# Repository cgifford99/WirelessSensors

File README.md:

# WirelessSensors
Wireless Sensors Flex Friday project repo

Here's a link to our Waffle.io management board: https://waffle.io/cgifford99/WirelessSensors/join

## Current Schedule
- [x] Project Proposal  | September 11th-September 30th
- [x] Research          | September 30th-October 7th
- [ ] Data pro design   | October 7th- December 23rd
- [ ] Testing/Debugging | December 23rd-April 7th 2017
- [ ] Finalize product  | March 3rd 2017-May 19th 2017
- [ ] Presentation      | May 19th 2017-June 9th 2017

# Wireless Sensors Proposal
## Abstract
The Wireless Sensor group’s overall goal is to create an easier and more cost-effective way to wirelessly transmit data from classroom   experiments from sensors through a communication chip to internet-enabled devices such as computers, laptops, tablets and smartphones. This system will allow students to easily customize how data is collected and manipulate data to fit their needs. It also allows teachers to view   the student’s data. Although this system will be useful in many fields, the project is going to initially focus on the educational market. This technology currently exists from other corporations, but it’s slow, expensive, complicated and unreliable. The team’s alternative will be faster, less expensive, user friendly and will deliver consistent results again and again. Furthermore, the current systems use wires, that get tangled and get lost. All of these wires can be eliminated with the use of radio communication and this is what the Wireless Sensor Team plans to do.

## Problem Statement
Currently there is no easy way to collect, store and share data from classroom science experiments simply by running the experiment and having data automatically appear on a shared website using low-cost components and inexpensive, yet effective software. Vernier is a company that produces a product along the lines of what we are creating, but it’s expensive, slow, and hard to access data. Products produced by Vernier, such as LabQuest, cost over $300 and need the use of another source, such as a PC, to process the collected data.

## Goals and Objectives
* Goal 1: Create a working prototype that sends information from a Raspberry Pi Zero/Arduino Micro to a Raspberry Pi 3.

  * Objective A: Discuss what teams are necessary, what project managing software to use, whether to use a Raspberry Pi Zero or an Arduino Micro to control the sensors and whether to make another prototype for the Rpi Zero or not.
  * Objective B: If the Rpi Zero is going to be used, code will need to be converted from the Arduino C++ language to C++ on the Rpi Zero.
  * Objective C: Create a prototype that includes the necessary components to interact with the Rpi 3 (the Hub).
  * Objective D: Debug data collection process and code (if necessary).

* Goal 2: Develop a cloud-based software for data storage and data transfer.

  * Objective A: Study Flask-SQLAlchemy (a framework to connect to a SQL database on the Rpi 3 and a browser on another device)
  * Objective B: Create and test a connection between the Rpi 3 SQL database and Flask-SQLAlchemy

* Goal 3: Finalize the product so that it both looks and works well for users.

  * Objective A: Design, order and solder a PCB (printed circuit board) that integrates with the Rpi Zero as well as the Rpi 3 in a more compact and visually attractive method.
  * Objective B: Use solidworks or another 3D design software to design an enclosure for the Rpi 3 and the Rpi Zero/Arduino Micro.
  * Objective C: Complete, debug and finish the product.
  
## Our Team
**Christopher Gifford**: Christopher is a Junior and project manager of the Wireless Sensors group. Last year he managed the sensors portion of the wireless group and learned a variety of other skills like 3D design, PCB design, and more C++ programming since then. 

**Lewis Woodard**: Lewis is a Sophomore at Baxter Academy for Technology and Science who is a part of the Wireless Sensors project for the second year. He hopes to focus his efforts in the project towards hardware and enclosures, which will include PCB design and using SolidWorks to design enclosures, cases, and other devices to contain sensors. Last year Lewis joined after completing the Pentathlon and worked on a combination of hardware, enclosures and software. Since last year, Lewis has gained more experience in C++ programming, CAD and more. Lewis plans to use this knowledge to focus mainly on hardware, pcb and 3D design, assisting on programming and software when he is needed.

**Connor Bell**: (NOTE: Connor is no longer involved with the project) Connor is a Junior at Baxter Academy for Technology and Science. He is a new addition to the Wireless Sensors project. He has taken multiple classes based around electronics and computer programming, and is currently learning as much as he can to have enough knowledge to be successful on this projects. Connor has programmed multiple web-based and non-web based programs in various languages such as Python and Javascript, both of which are relevant to the progress of this project.

**Curtis**: 
Curtis is a Sophomore at Baxter Academy for Technology and Science. He is also a new addition to the Wireless Sensors project. He has taken multiple classes based around electronics and computer programming. Curtis plans to concentrate on programming so that he be a productive member of the group.

**Ryan Cunningham**: Ryan is a freshman a Baxter. He is also a new addition to the Wireless Sensors project. He has lots of experience in HTML and CSS, he also is skilled in GUI design and graphics works. 

## Timeline
Currently unavailable

## Resources
* The school has tools like 3d printing software and equipment, soldering irons and other useful PCB design tools.
* Alan Lukas, Hal, Wells and Amory have backgrounds in programming, 3D design and PCB design and their knowledge will be very useful in the project.
* Currently an arduino prototype (Sensor prototype) and a Raspberry Pi 3 prototype (Hub prototype), are functioning from last year.    However, the Arduino did not have sufficient memory to hold a large number of different data acquisition formats.    The current plan is to use a RPi Zero instead for the Arduino for the sensor prototype.
* Purchase a  variety of Vernier sensors or borrow them as required from Baxter’s inventory.

## Constraints
* The team’s experience in PCB design, C++ programming, 3D design and other skill sets will influence how smoothly the project goes.
* There is not enough time this year to set-up a business and market the product to schools and other educational services.
* Accidents like damaging the circuits or short-circuiting them has been a problem in the past.
* There will be plenty of distractions and time constraints, but the team will use detailed schedules (Kanban and Gantter) to stay on track.

## Budget
Currently unavailable

## Deliverables
The final product will be a marketable platform to use in a classroom environment for experiments and laboratory tests in different subjects including physics, chemistry, and others. It will be made up of a Raspberry Pi Zeros (sensors) and a larger Raspberry Pi (hub). The hub will store and organize all data into a database and then send these data to a common cloud-based web server. Students can then connect to this web site to compare results of the data collected in the various class experiments. Note that data can also be collected from field experiments and then sent up to the cloud based server once the sensors connect to the RPi hub.

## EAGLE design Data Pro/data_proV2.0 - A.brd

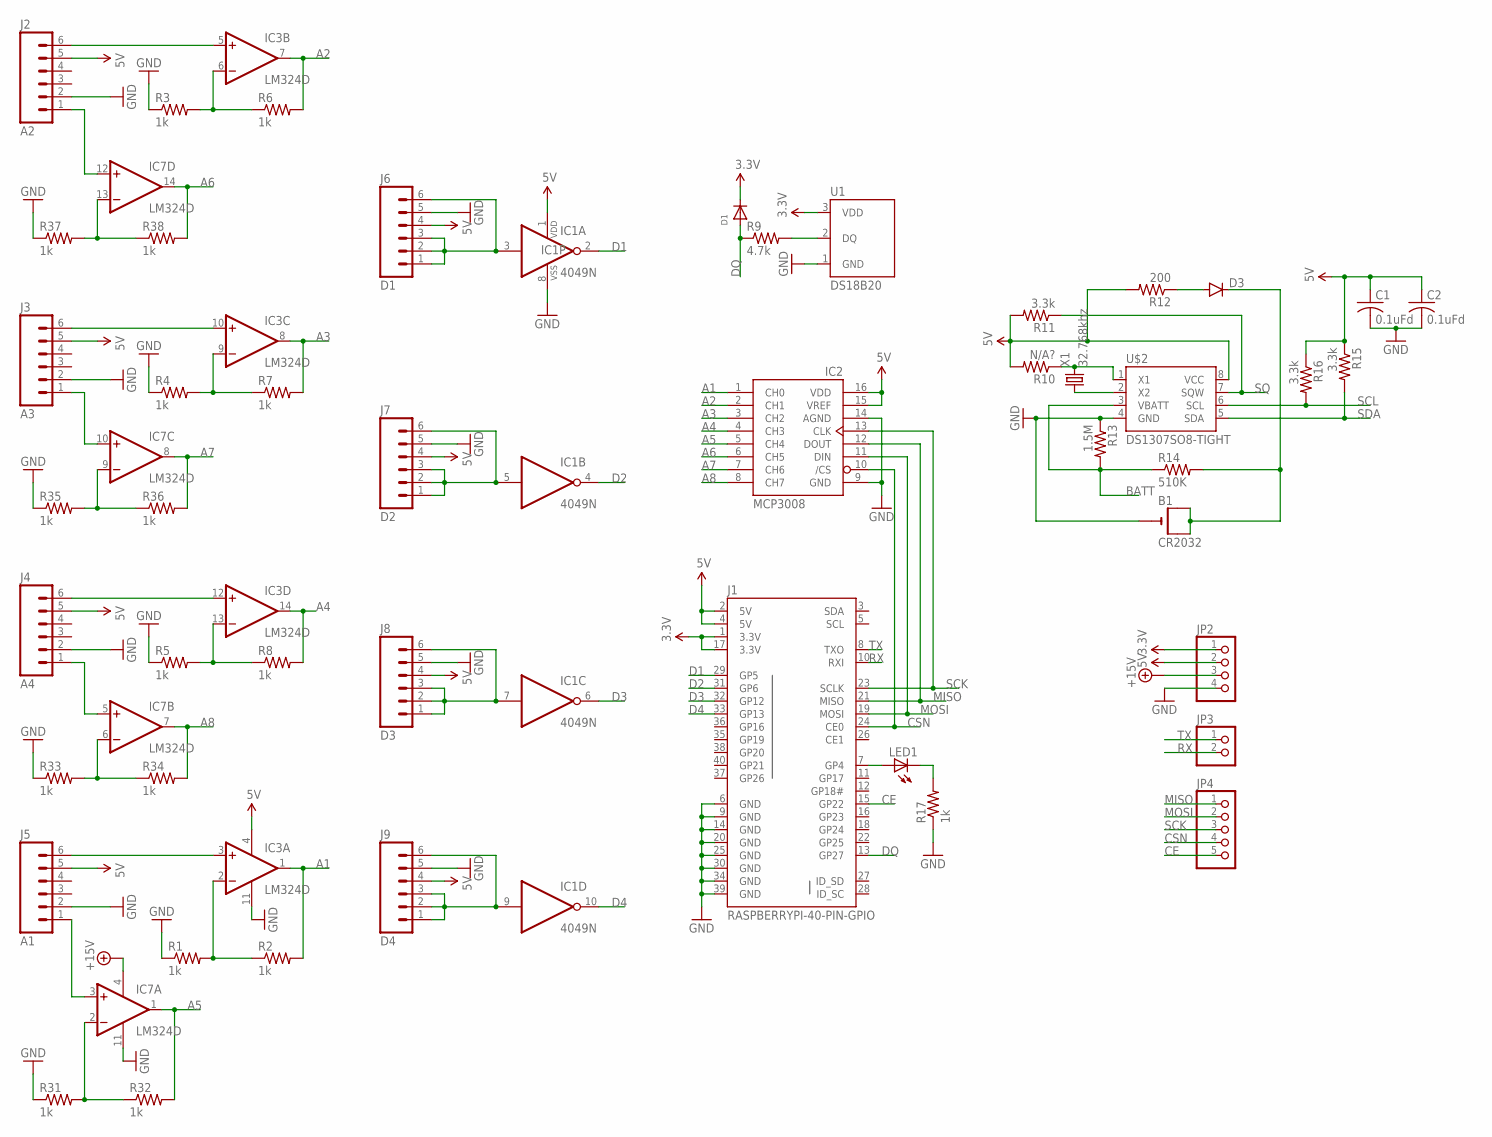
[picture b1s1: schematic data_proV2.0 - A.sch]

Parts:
B1: CR2032; CR2032-SMD
C1, C2: 0.1uFd; C0805
D1: DIODESOD-323F; SOD-323F
D3: DIODESMB; SMB-DIODE
IC1: 4049N; DIL16
IC2: MCP3008; DIL16
IC3, IC7: LM324D; SO14
J1: RASPBERRYPI-40-PIN-GPIO; 2X20-SHROUDED
J2: A2; BTA
J3: A3; BTA
J4: A4; BTA
J5: A1; BTA
J6: D1; BTD
J7: D2; BTD
J8: D3; BTD
J9: D4; BTD
JP2: PINHD-1X4; 1X04
JP3: PINHD-1X2; 1X02
JP4: PINHD-1X5; 1X05
LED1: LEDCHIP-LED0805; CHIP-LED0805
R1, R2, R3, R4, R5, R6, R7, R8, R17, R31, R32, R33, R34, R35, R36, R37, R38: 1k; R0805
R9: 4.7k; R0805
R10: N/A?; R0805
R11, R15, R16: 3.3k; R0805
R12: 200; R0805
R13: 1.5M; R0805
R14: 510K; R0805
U1: DS18B20; TO-92-AMMO
U$2: DS1307SO8-TIGHT; SO08-TIGHT
X1: 32.768khz; TC38H

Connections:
3.3V: D1.C, J1.1 (3.3V), J1.17 (3.3V), JP2.1, U1.3 (VDD)
5V: C1.1, C2.1, IC1.1 (VDD), IC2.15 (VREF), IC2.16 (VDD), IC3.4 (V+), J1.2 (5V), J1.4 (5V), J2.5, J3.5, J4.5, J5.5, J6.4, J7.4, J8.4, J9.4, JP2.2, R10.2, R11.2, R12.2, R15.1, R16.1, U$2.8 (VCC)
+15V: IC7.4 (V+), JP2.3
A1: IC2.1 (CH0), IC3.1 (OUT), R2.2
A2: IC2.2 (CH1), IC3.7 (OUT), R6.2
A3: IC2.3 (CH2), IC3.8 (OUT), R7.2
A4: IC2.4 (CH3), IC3.14 (OUT), R8.2
A5: IC2.5 (CH4), IC7.1 (OUT), R32.2
A6: IC2.6 (CH5), IC7.14 (OUT), R38.2
A7: IC2.7 (CH6), IC7.8 (OUT), R36.2
A8: IC2.8 (CH7), IC7.7 (OUT), R34.2
BATT: R13.2, R14.1, U$2.3 (VBATT)
CE: J1.15 (GP22), JP4.5
CSN: IC2.10 (/CS), J1.24 (CE0), JP4.4
D1: IC1.2 (O), J1.29 (GP5)
D2: IC1.4 (O), J1.31 (GP6)
D3: IC1.6 (O), J1.32 (GP12)
D4: IC1.10 (O), J1.33 (GP13)
DQ: D1.A, J1.13 (GP27), R9.1
GND: B1.-, C1.2, C2.2, IC1.8 (VSS), IC2.9 (GND), IC2.14 (AGND), IC3.11 (V-), IC7.11 (V-), J1.6 (GND), J1.9 (GND), J1.14 (GND), J1.20 (GND), J1.25 (GND), J1.30 (GND), J1.34 (GND), J1.39 (GND), J2.2, J3.2, J4.2, J5.2, J6.5, J7.5, J8.5, J9.5, JP2.4, R1.1, R3.1, R4.1, R5.1, R13.1, R17.1, R31.1, R33.1, R35.1, R37.1, U1.1 (GND), U$2.4 (GND)
MISO: IC2.12 (DOUT), J1.21 (MISO), JP4.1
MOSI: IC2.11 (DIN), J1.19 (MOSI), JP4.2
unnamed: U$2.2 (X2), X1.1
unnamed: R10.1, U$2.1 (X1), X1.2
unnamed: B1.+$1 (+), B1.+$2 (+1), D3.C, R14.2
unnamed: J1.7 (GP4), LED1.A
unnamed: IC3.2 (-IN), R1.2, R2.1
unnamed: R9.2, U1.2 (DQ)
unnamed: IC3.13 (-IN), R5.2, R8.1
unnamed: IC3.6 (-IN), R3.2, R6.1
unnamed: D3.A, R12.1
unnamed: IC1.3 (I), J6.1, J6.2, J6.3, J6.6
unnamed: IC1.5 (I), J7.1, J7.2, J7.3, J7.6
unnamed: IC1.7 (I), J8.1, J8.2, J8.3, J8.6
unnamed: IC1.9 (I), J9.1, J9.2, J9.3, J9.6
unnamed: IC3.9 (-IN), R4.2, R7.1
unnamed: LED1.C, R17.2
unnamed: IC3.3 (+IN), J5.6
unnamed: IC7.2 (-IN), R31.2, R32.1
unnamed: IC7.3 (+IN), J5.1
unnamed: IC7.6 (-IN), R33.2, R34.1
unnamed: IC7.9 (-IN), R35.2, R36.1
unnamed: IC7.13 (-IN), R37.2, R38.1
unnamed: IC7.12 (+IN), J2.1
RX: J1.10 (RXI), JP3.2
S1-5V1: IC3.5 (+IN), J2.6
S1-5V2: IC3.10 (+IN), J3.6
S1-5V3: IC7.5 (+IN), J4.1
S1-5V4: IC3.12 (+IN), J4.6
S1-5V5: IC7.10 (+IN), J3.1
SCK: IC2.13 (CLK), J1.23 (SCLK), JP4.3
SCL: R16.2, U$2.6 (SCL)
SDA: R15.2, U$2.5 (SDA)
SQ: R11.1, U$2.7 (SQW)
TX: J1.8 (TXO), JP3.1

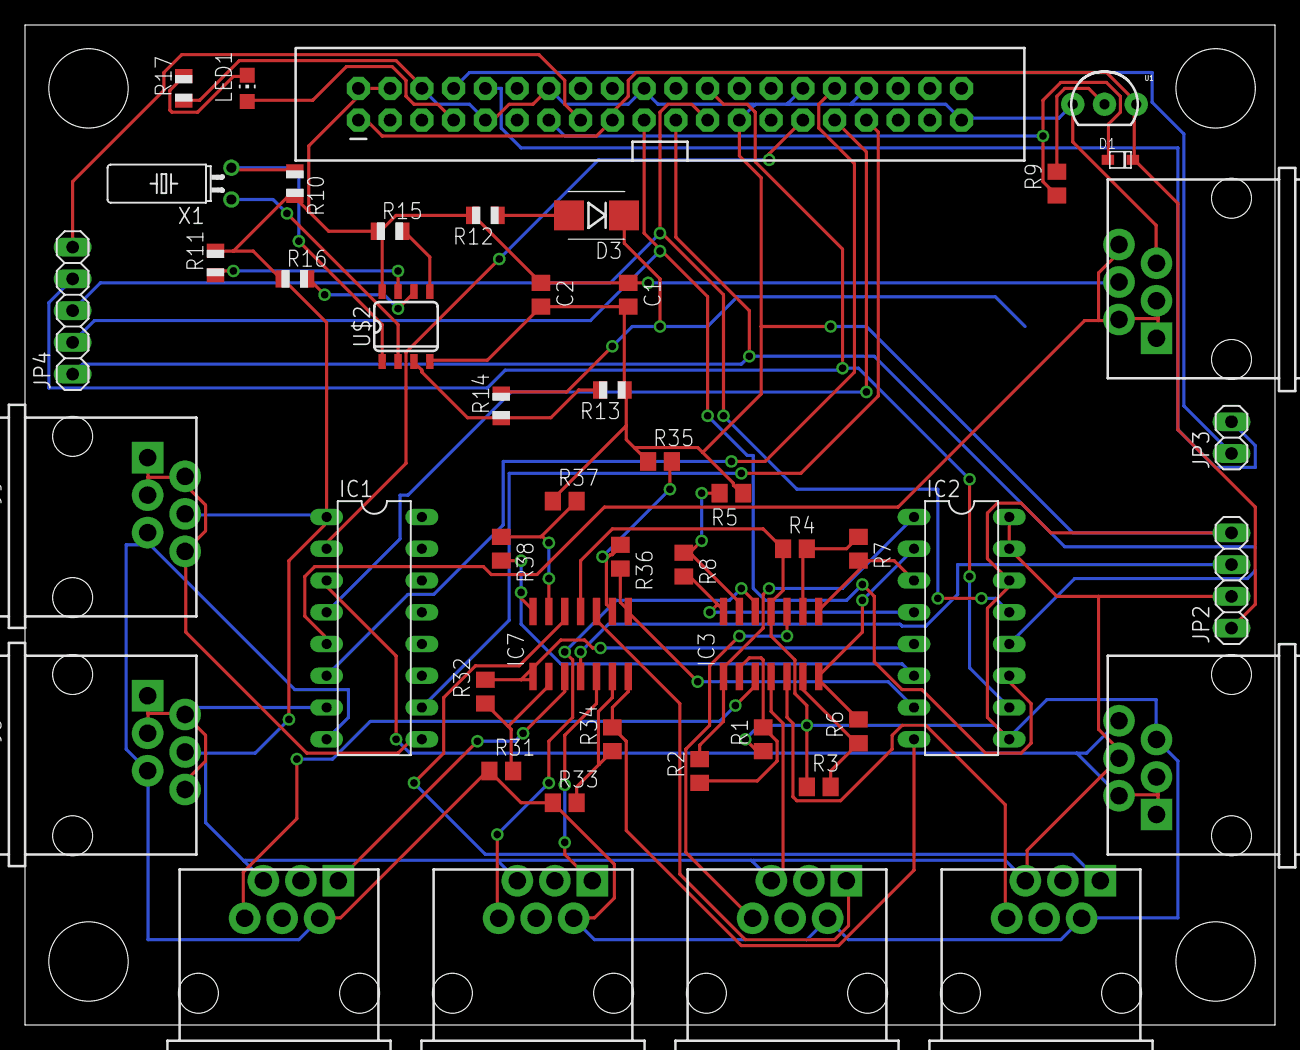
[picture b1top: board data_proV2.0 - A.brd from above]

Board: 2 copper layers, 100.0 x 80.0 mm, 50 parts (1 on the bottom side), 55 nets.

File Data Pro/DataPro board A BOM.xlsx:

Part Name | Value | Device | Package | Description | Retailer | Retailer Part # | Manufacturer Part # | Quantity
B1 | CR2032 | CR2032SMT | CR2032-SMD |  | Digikey | BRX1-2032-SMCT-ND | BRX1-2032-SM | 1.0
C1 | 0.1uFd | C-USC0805 | C0805 | CAPACITOR, American symbol | Digikey | 311-1142-1-ND | CC0805KRX7R7BB104 | 2.0
D1 |  | DIODESOD-323F | SOD-323F | Diode | Digikey | MM3Z3V3BTR-ND | MM3Z3V3B | 1.0
D3 |  | DIODESMB | SMB-DIODE | Diode | Digikey | 1SMB5928BT3GOSCT-ND | 1SMB5928BT3G | 1.0
IC1 | 4049N | 4049N | DIL16 | Hex inverting BUFFER | Digikey | 296-29273-1-ND | CD74HC4049NSR | 1.0
IC2 | MCP3008 | MCP3008 | DIL16 |  | Digikey | MCP3008-I/P-ND | MCP3008-I/P | 1.0
IC3, IC7 | LM324D | LM324D | SO14 | OP AMP | Digikey | 497-1580-1-ND | LM324DT | 2.0
J1 | RASPBERRYPI-40-PIN-GPIO | RASPBERRYPI-40-PIN-GPIO | 2X20-SHROUDED | Raspberry Pi GPIO Header | Digikey | 1528-1785-ND | 2222.0 | 1.0
J2-J5 | A2 | M06VERNIER-ANALOG | BTA | Header 6 | https://www.sparkfun.com/products/12753 |  |  | 4.0
J6-J9 | D1 | M06VERNIER-DIGITAL | BTD | Header 6 | https://www.sparkfun.com/products/12754 |  |  | 4.0
JP2 |  | PINHD-1X4 | 1X04 | PIN HEADER
JP3 |  | PINHD-1X2 | 1X02 | PIN HEADER
JP4 |  | PINHD-1X5 | 1X05 | PIN HEADER
LED1 |  | LEDCHIP-LED0805 | CHIP-LED0805 | LED | Digikey | 475-1278-1-ND | LS R976-NR-1 | 1.0
R1-R8, R10, R17-R26 | 1k | R-US_R0805 | R0805 | RESISTOR, American symbol | Digikey | 311-1.0KARCT-ND | RC0805JR-071KL | 17.0
R9 | 4.7k | R-US_R0805 | R0805 | RESISTOR, American symbol | Digikey | 311-4.70KCRCT-ND | RC0805FR-074K7L | 1.0
R11, R15, R16 | 3.3k | R-US_R0805 | R0805 | RESISTOR, American symbol | Digikey | 311-3.3KARCT-ND | RC0805JR-073K3L | 3.0
R12 | 200.0 | R-US_R0805 | R0805 | RESISTOR, American symbol | Digikey | 311-200CRTR-ND | RC0805FR-07200RL | 1.0
R13 | 1.5M | R-US_R0805 | R0805 | RESISTOR, American symbol | Digikey | 311-1.5MARTR-ND | RC0805JR-071M5L | 1.0
R14 | 510K | R-US_R0805 | R0805 | RESISTOR, American symbol | Digikey | 311-510KARCT-ND | RC0805JR-07510KL | 1.0
U$2 | DS1307SO8-TIGHT | DS1307SO8-TIGHT | SO08-TIGHT | I2C real-time clock with battery backup. | Digikey | DS1307Z+T&RCT-ND | DS1307Z+T&R | 1.0
U1 | DS18B20 | DS18B20 | TO-92-AMMO | DS18B20 1-wire temperature sensor | Digikey | DS18B20+-ND | DS18B20+ | 1.0
X1 | 32.768khz | CRYSTALTC38H | TC38H | CRYSTAL | Digikey | 535-9034-ND | AB38T-32.768KHZ | 1.0

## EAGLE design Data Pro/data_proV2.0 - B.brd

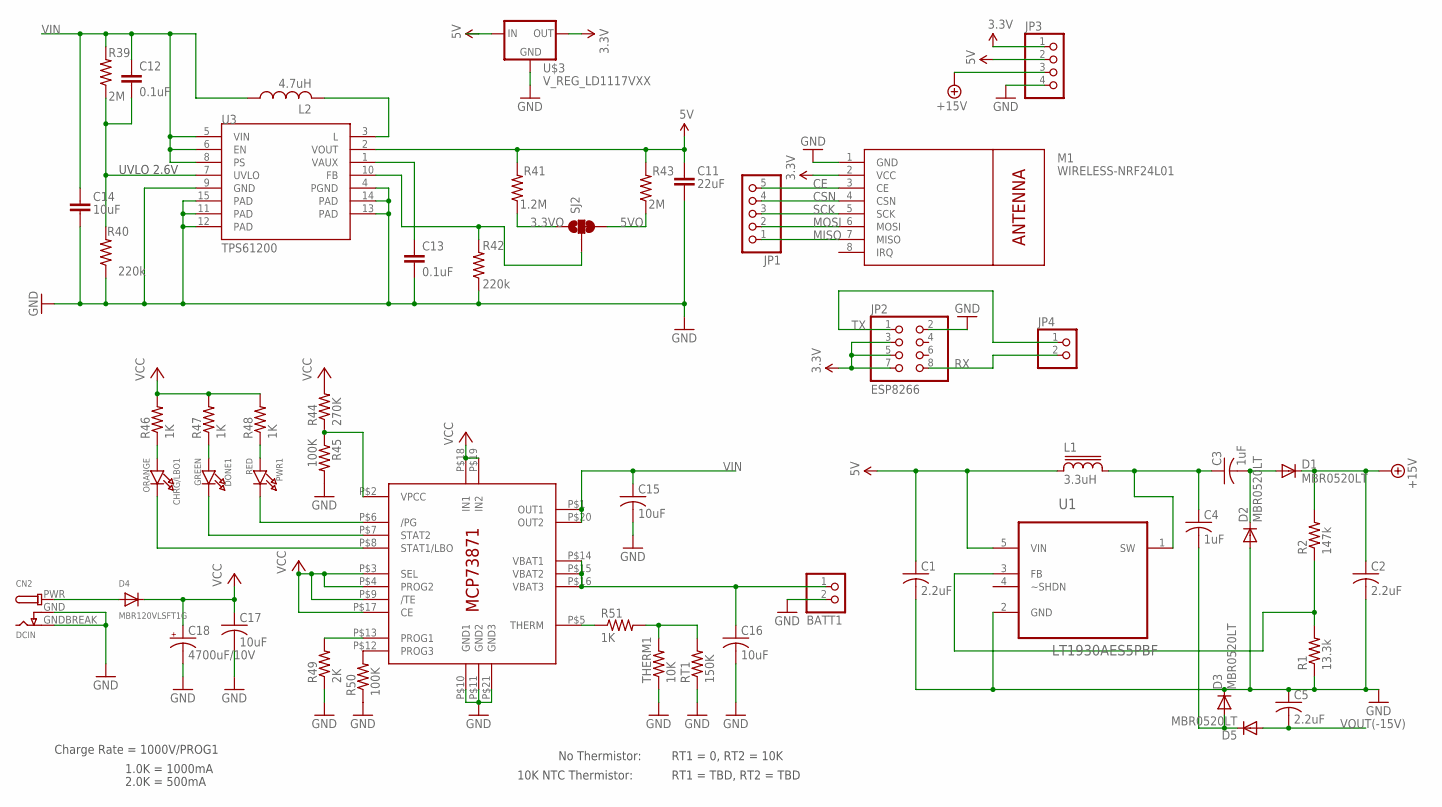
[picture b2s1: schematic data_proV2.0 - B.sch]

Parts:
BATT1: JST_2PIN-SMT-RA; JST-PH-2-SMT-RA
C1: 2.2uF; C0805
C2, C5: 2.2uF; C1206
C3, C4: 1uF; C1206
C11: 22uF; 0805
C12, C13: 0.1uF; 0603-CAP
C14: 10uF; 1206
C15, C16, C17: 10uF; C0805K
C18: 4700uF/10V; E5-13
CHRG/LBO1: ORANGE; CHIPLED_0805_NOOUTLINE
CN2: DCIN; DCJACK_2MM_SMT
D1, D2, D3, D5: MBR0520LT; SOD123
D4: MBR120VLSFT1G; SOD-123
DONE1: GREEN; CHIPLED_0805_NOOUTLINE
IC8: MCP73871; QFN20_4MM
JP1: PINHD-1X5; 1X05
JP2: ESP8266; 2X04
JP3: PINHD-1X4; 1X04
JP4: PINHD-1X2; 1X02
L1: 3.3uH; CR43
L2: 4.7uH; L3225M
M1: WIRELESS-NRF24L01
PWR1: RED; CHIPLED_0805_NOOUTLINE
R1: 13.3k; R0805
R2: 147k; R0805
R39, R43: 2M; 0603-RES
R40, R42: 220k; 0603-RES
R41: 1.2M; 0603-RES
R44: 270K; R0805
R45, R50: 100K; R0805
R46, R47, R48: 1K; R0805
R49: 2K; 0805-THM
R51: 1K; M0805
RT1: 150K; M0805
SJ2: SOLDERJUMPER_2WAYPASTE2&3; SJ_3_PASTE2&3
THERM1: 10K; 0805-THM
U1: LT1930AES5PBF; SOT95P280X145-5N
U3: TPS61200; QFN-10_PAD
U$3: V_REG_LD1117VXX; 78XXL

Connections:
3.3V: JP2.3, JP2.5, JP2.7, JP3.1, M1.2 (VCC), U$3.GND (OUT)
3.3VO: R41.1, SJ2.1
5V: C1.1, C11.1, JP3.2, L1.1, R41.2, R43.2, U1.5 (VIN), U3.2 (VOUT), U$3.OUT (IN)
5VO: R43.1, SJ2.3
+15V: C2.1, D1.C, JP3.3, R2.2
BATT2: BATT1.1 (2), C16.1, IC8.P$14 (VBAT1), IC8.P$15 (VBAT2), IC8.P$16 (VBAT3)
CE: JP1.5, M1.3 (CE)
CSN: JP1.4, M1.4 (CSN)
FB1: R42.2, SJ2.2, U3.10 (FB)
GND: BATT1.2 (1), C1.2, C2.2, C5.1, C11.2, C13.2, C14.2, C15.2, C16.2, C17.2, C18.-, CN2.GND (GNDBREAK), CN2.GNDBREAK (GND), D2.A, D3.C, IC8.P$10 (GND1), IC8.P$11 (GND2), IC8.P$21 (GND3), JP2.2, JP3.4, M1.1 (GND), R1.1, R40.1, R42.1, R45.2, R49.1, R50.1, RT1.1, THERM1.1, U1.2 (GND), U3.4 (PGND), U3.9 (GND), U3.11 (PAD), U3.12 (PAD), U3.13 (PAD), U3.14 (PAD), U3.15 (PAD), U$3.IN (GND)
MISO: JP1.1, M1.7 (MISO)
MOSI: JP1.2, M1.6 (MOSI)
unnamed: C4.2, D3.A, D5.C
unnamed: C3.1, C4.1, L1.2, U1.1 (SW)
unnamed: R1.2, R2.1, U1.3 (FB)
unnamed: C3.2, D1.A, D2.C
unnamed: L2.2, U3.3 (L)
unnamed: C13.1, U3.1 (VAUX)
unnamed: IC8.P$2 (VPCC), R44.1, R45.1
unnamed: IC8.P$6 (/PG), PWR1.C
unnamed: DONE1.C, IC8.P$7 (STAT2)
unnamed: CHRG/LBO1.C, IC8.P$8 (STAT1/LBO)
unnamed: CHRG/LBO1.A, R46.1
unnamed: DONE1.A, R47.1
unnamed: PWR1.A, R48.1
unnamed: IC8.P$12 (PROG3), R50.2
unnamed: IC8.P$13 (PROG1), R49.2
unnamed: IC8.P$5 (THERM), R51.1
unnamed: R51.2, RT1.2, THERM1.2
unnamed: CN2.PWR, D4.A
RX: JP2.8, JP4.2
SCK: JP1.3, M1.5 (SCK)
TX: JP2.1, JP4.1
UVLO1: C12.2, R39.1, R40.2, U3.7 (UVLO)
VCC: C17.1, C18.+, D4.C, IC8.P$3 (SEL), IC8.P$4 (PROG2), IC8.P$9 (/TE), IC8.P$17 (CE), IC8.P$18 (IN1), IC8.P$19 (IN2), R44.2, R46.2, R47.2, R48.2
VIN: C12.1, C14.1, C15.1, IC8.P$1 (OUT1), IC8.P$20 (OUT2), L2.1, R39.2, U3.5 (VIN), U3.6 (EN), U3.8 (PS)
VOUT(-15V): C5.2, D5.A

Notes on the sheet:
UVLO 2.6V
Charge Rate = 1000V/PROG1
1.0K = 1000mA
2.0K = 500mA
No Thermistor:
10K NTC Thermistor:
RT1 = 0, RT2 = 10K
RT1 = TBD, RT2 = TBD

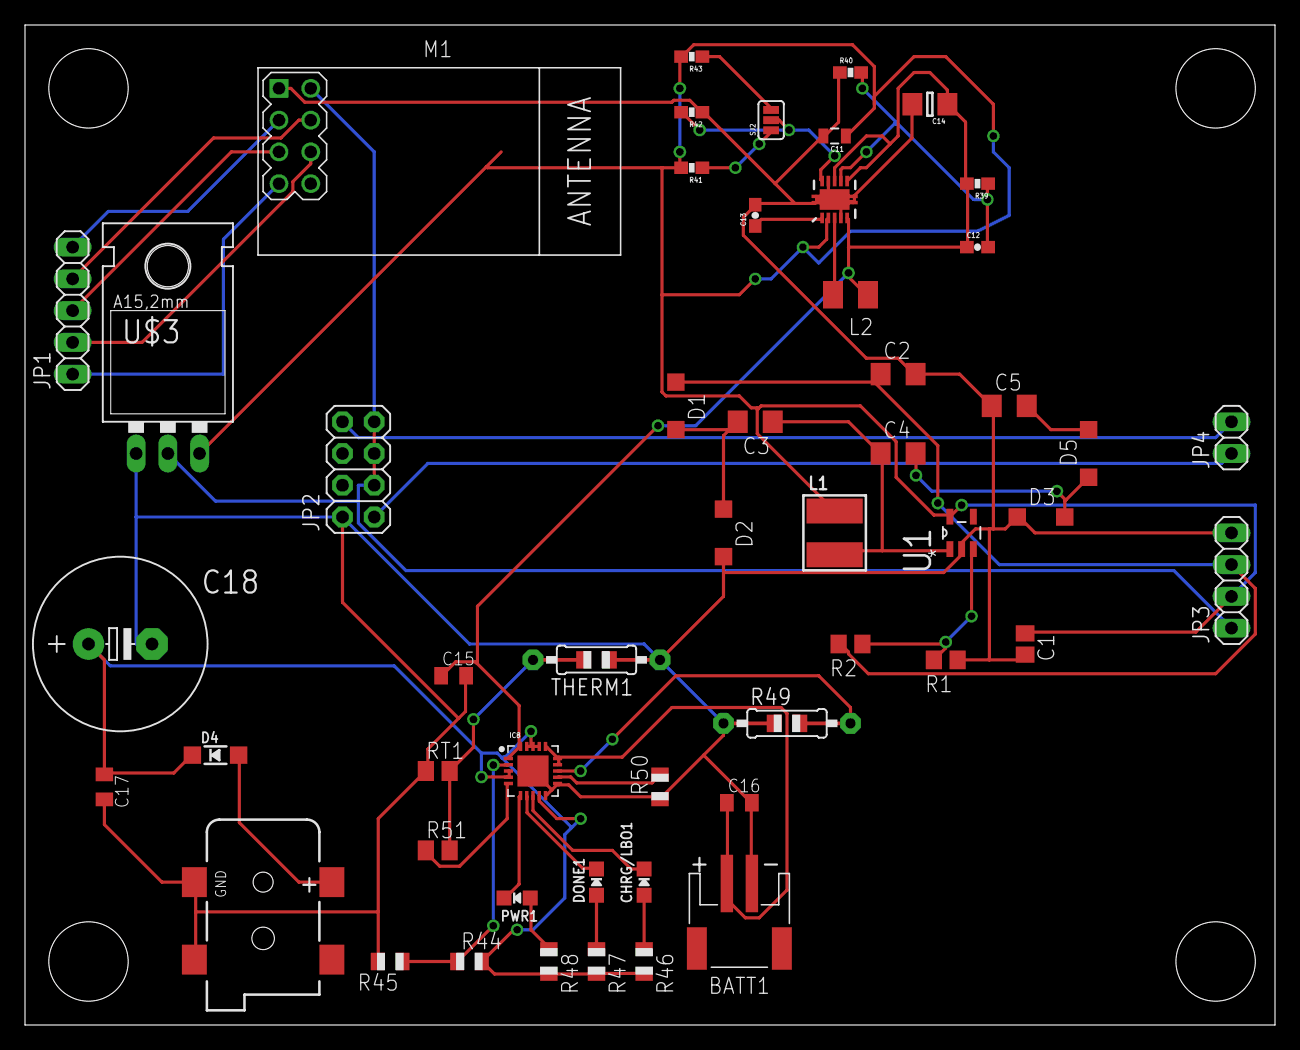
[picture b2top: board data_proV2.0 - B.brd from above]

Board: 2 copper layers, 100.0 x 80.0 mm, 52 parts (0 on the bottom side), 37 nets.

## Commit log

2016-09-09 Test Commit
    Its the first commit wow
2016-09-29 Updated README
    Now includes a schedule and project proposal
2016-11-13 Data Pro Schematic (Unfinished)
2016-11-28 Data pro schematic 11/28/16
2016-12-09 Data pro update and Lewis' python code
2017-01-10 Data pro update v1.2
    The schematic is complete, working on the board.
2017-01-13 adding web client
2017-01-19 Data pro update v1.2 (Complete)
2017-01-20 UI Files Update
    Added some files to be used for the UI
2017-01-20 Data pro complete
2017-01-27 More data pro updates
    Sorry
2017-03-15 First prototype complete
2017-04-07 Pushing progress on server and client code architecture.
2017-04-07 The newest version of the HTML WIP pages
2017-04-07 Fixed some file names and removed a few old ones
2017-04-07 Small edit
2017-04-07 Cleaned up some uwanted/rejected files
2017-04-07 More organization
2017-04-07 Fixed rendering issue
2017-04-07 CSS edits to line up graph
2017-04-07 CSS fixes, correcting merge error from before.
2017-04-07 Adding message to empty chart box.
2017-04-07 Small change
2017-04-07 Amazing update, fixed issues and modifed thingys
2017-04-07 Enabling MDL radio buttons.
2017-04-07 Made some small changes to Index.html to make it adequately lit
2017-04-14 Memes?
2017-04-14 progress on load screen.
2017-04-14 Changed tab 2 to active
2017-04-14 Fixed a few small files
2017-04-14 Adding loading widget.
2017-04-14 A few small changes
2017-04-14 Added some data to the secondary item
2017-04-14 Added some padding to the sides of the loading screen plus added a loading text to make it look a bit better
2017-04-14 configuring sever-side api
2017-04-28 sewtting up lewis's computer for mysql
2017-04-28 Not to big of changes, small things
2017-04-28 More small things
2017-04-28 update to api tester
2017-04-28 progress on api deployment
2017-04-28 Refactoring client.

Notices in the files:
parts and their libraries:
SparkFun-DiscreteSemi: Licensing: Creative Commons ShareAlike 4.0 International - https://creativecommons.org/licenses/by-sa/4.0
inductor-sumida: Copyright (C) 2008, Bob Starr
